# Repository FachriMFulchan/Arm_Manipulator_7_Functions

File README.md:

# Arm_Manipulator_7_Functions
Ini merupakan data dokumentasi dari Proyek Akhir kami yang berjudul "Rancang Bangun Arm Manipulator 7 Functions dan Master Controller" di Politeknik Manufaktur Negeri Bandung

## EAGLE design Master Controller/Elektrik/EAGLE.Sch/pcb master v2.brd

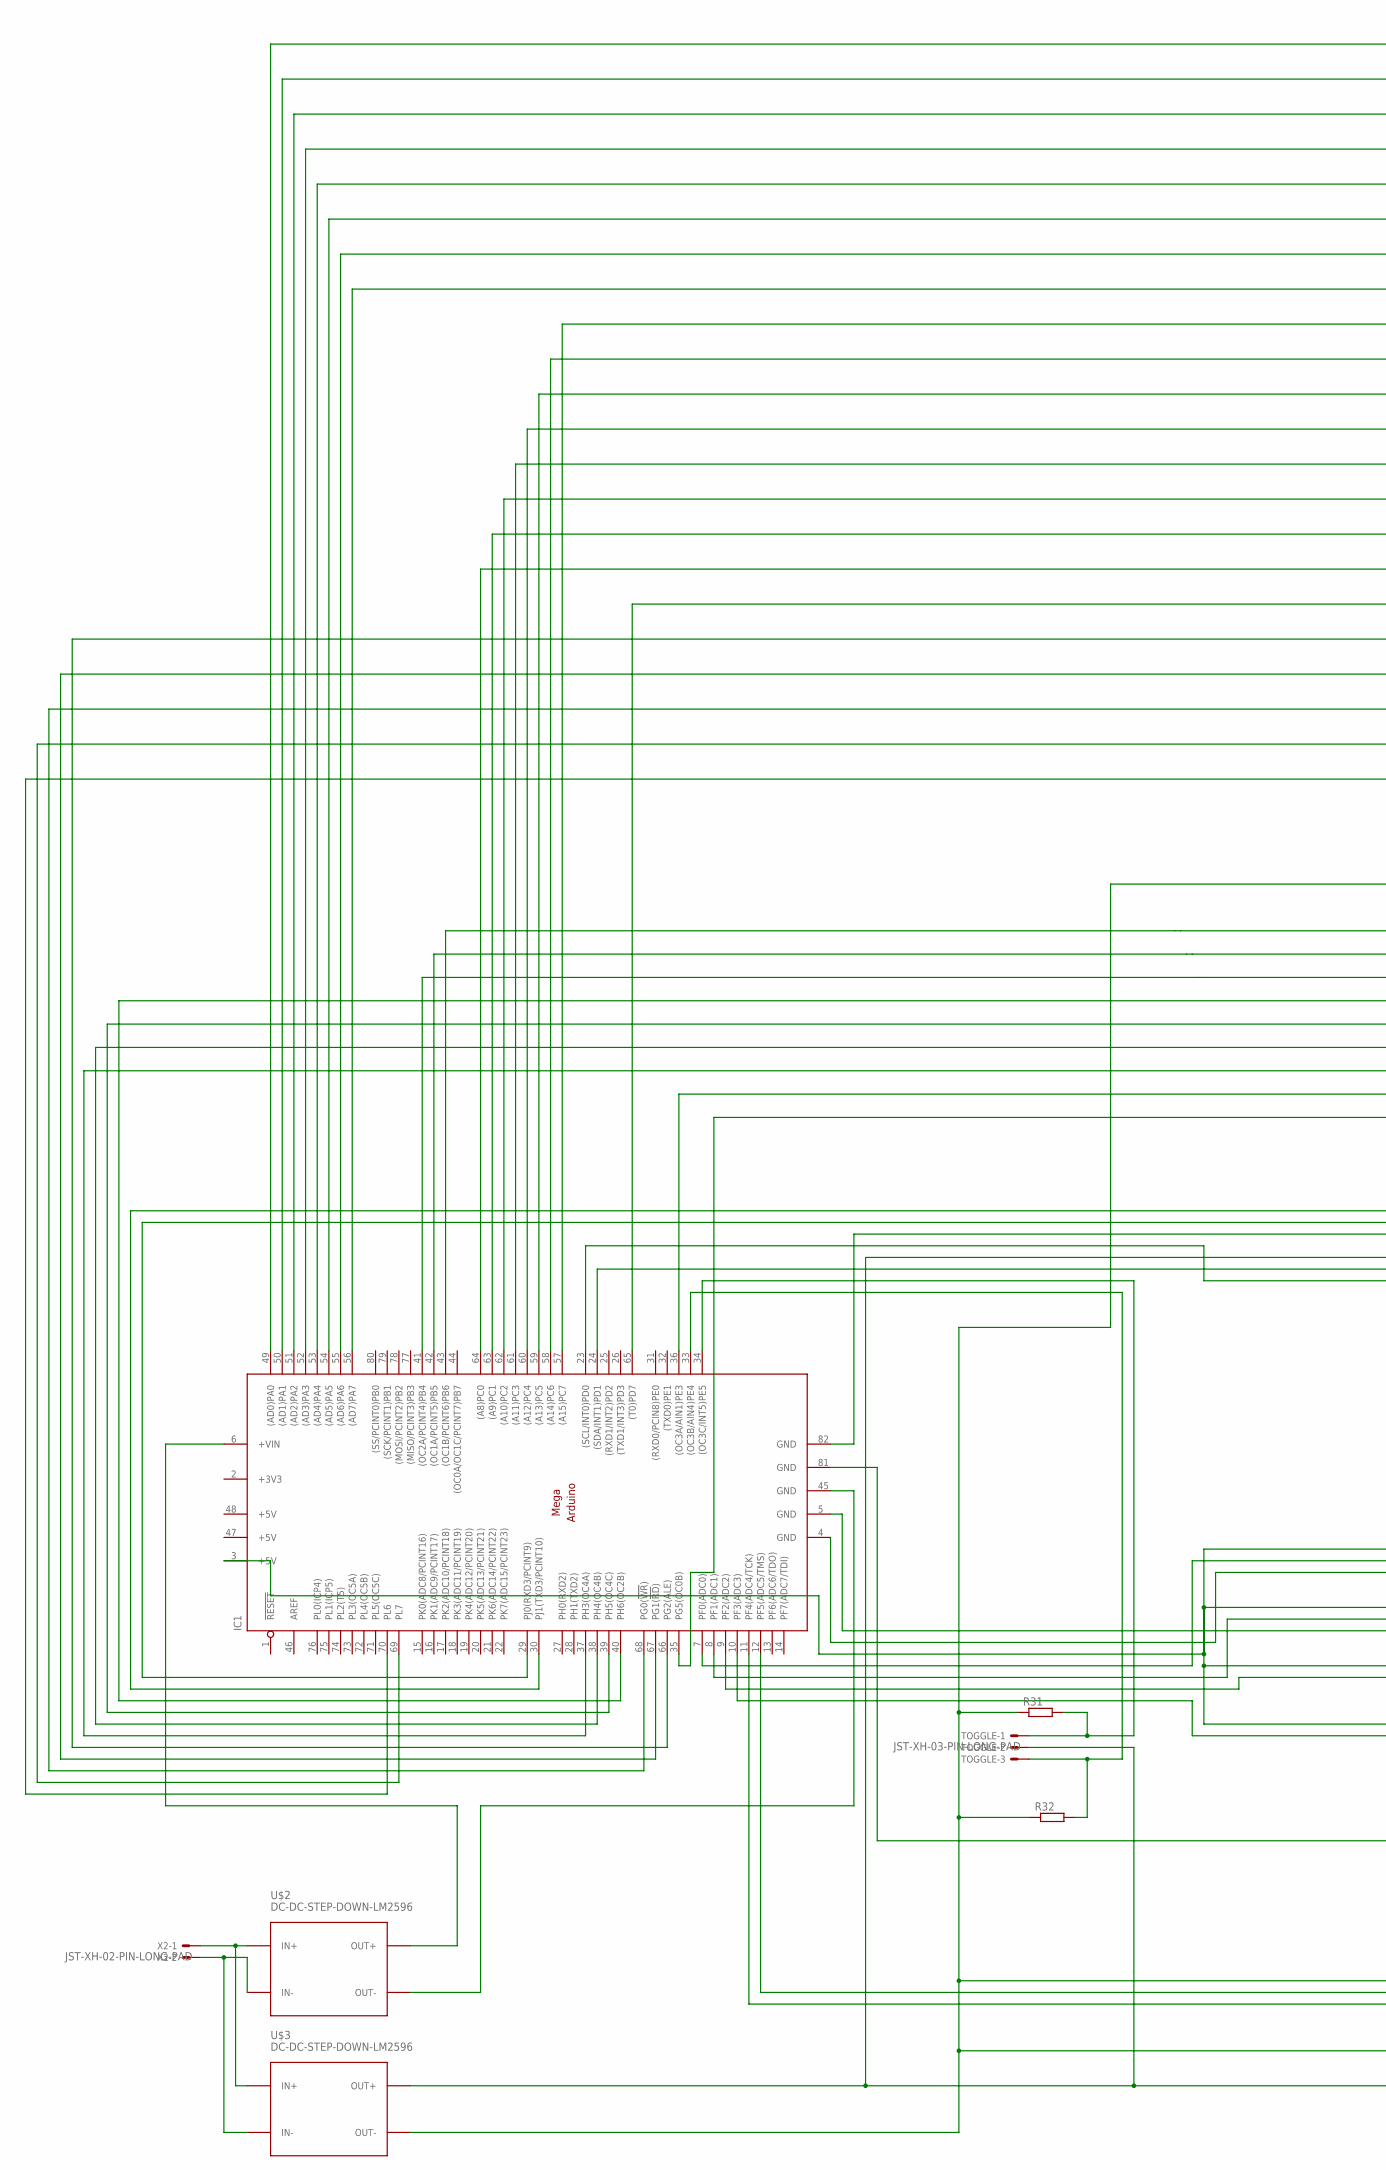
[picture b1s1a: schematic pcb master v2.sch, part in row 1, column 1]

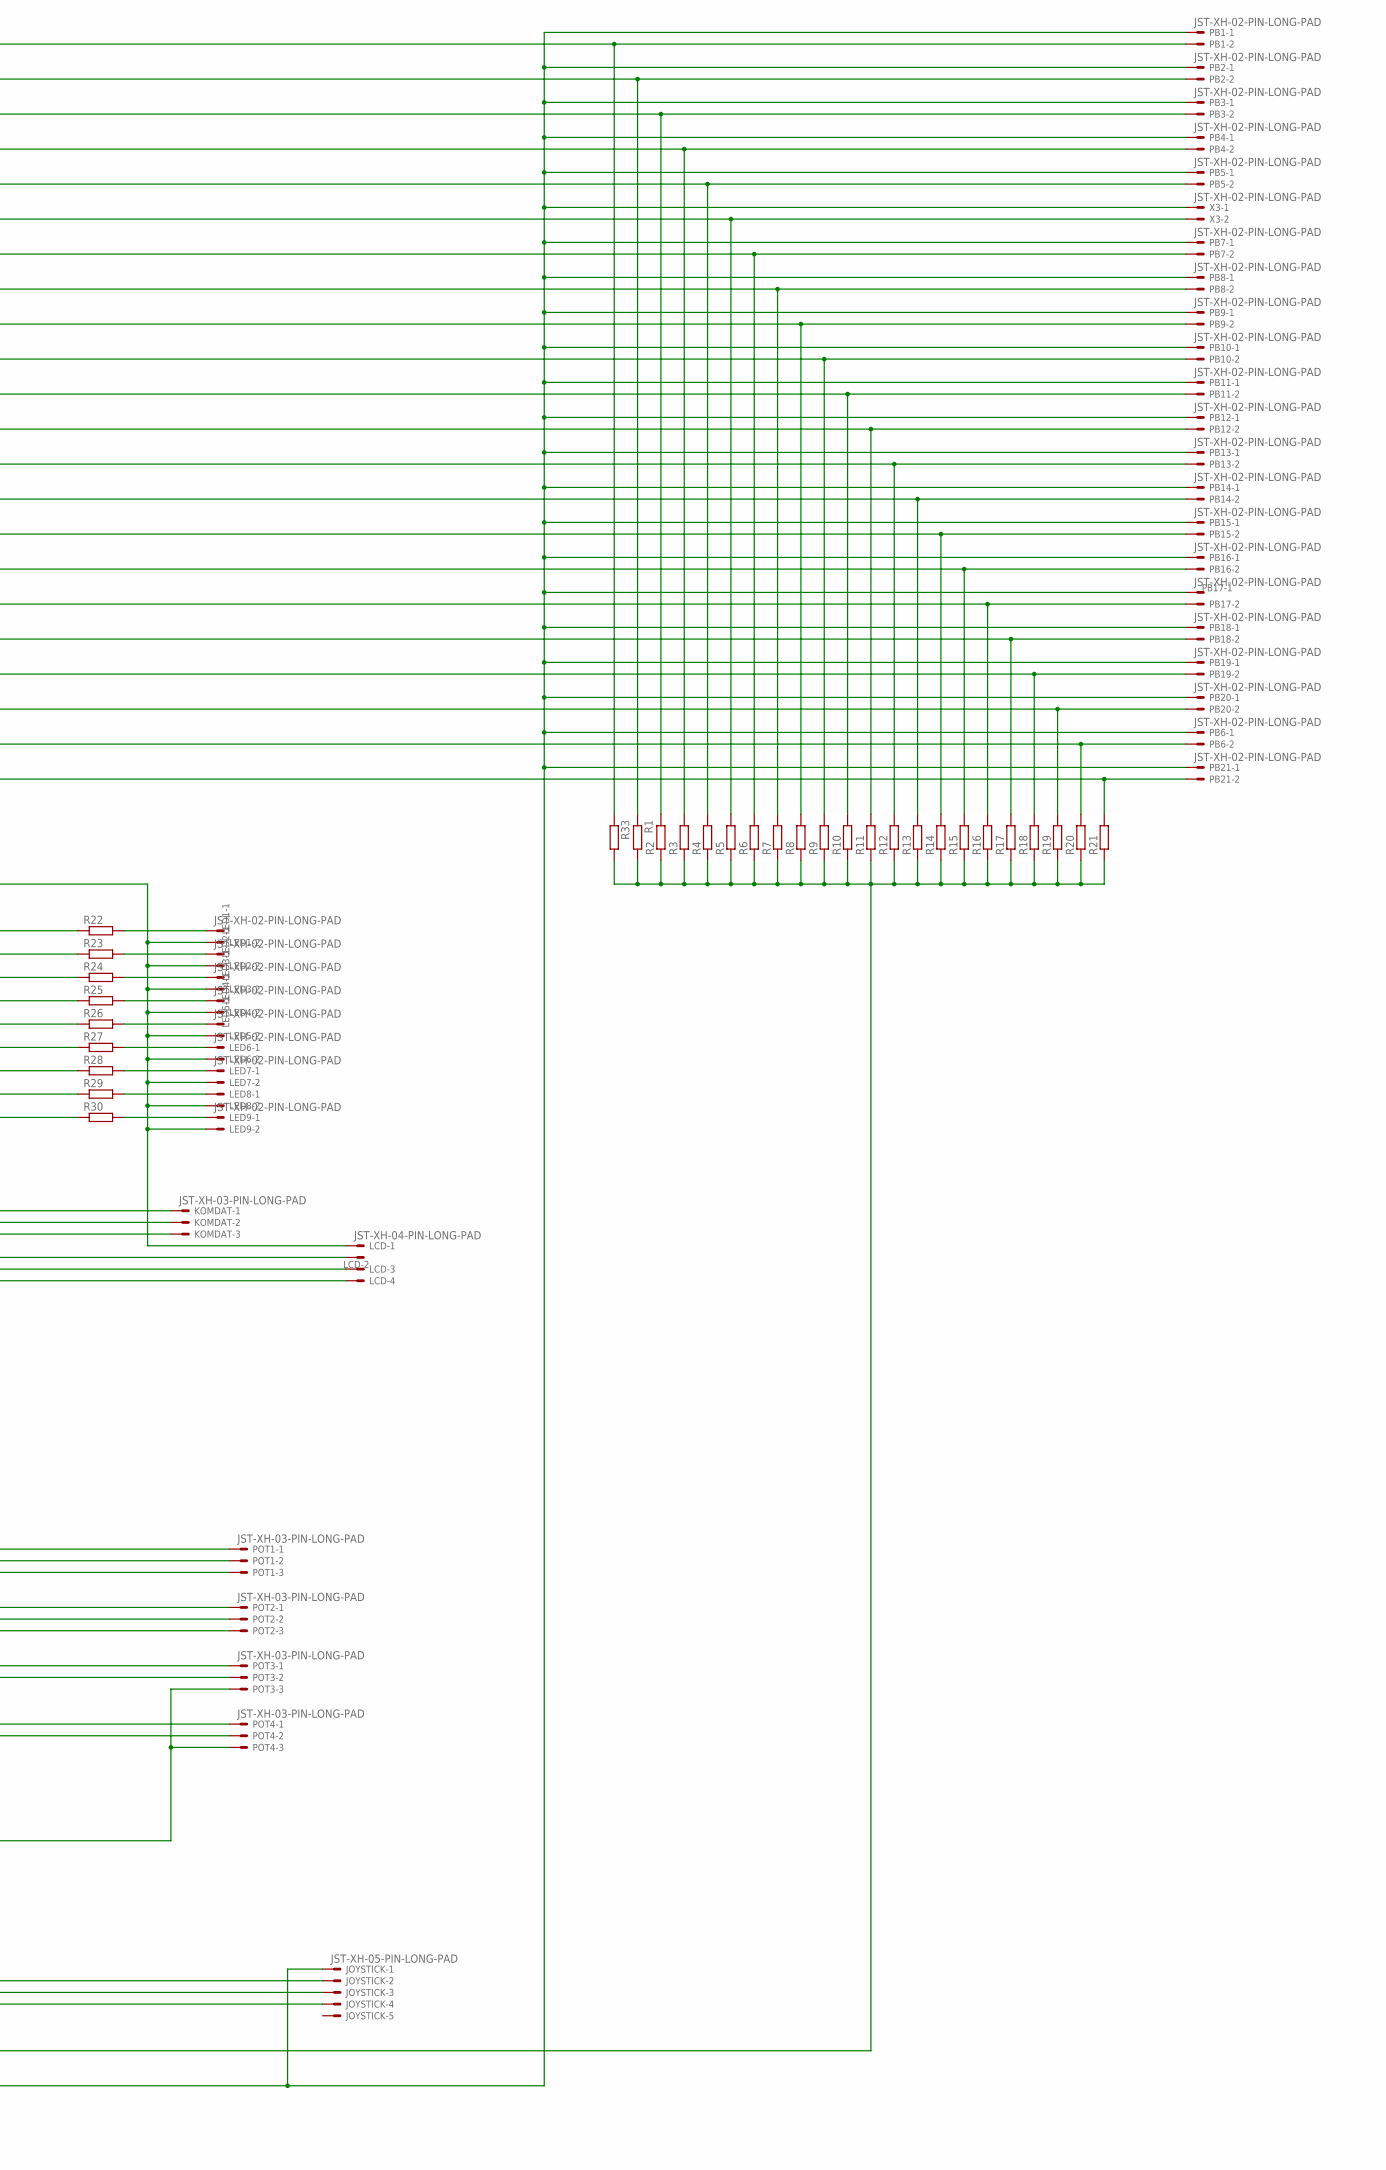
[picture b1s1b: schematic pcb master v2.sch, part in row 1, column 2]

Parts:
IC1: MEGAARDUINO_1; MEGA_ARDUINO
JOYSTICK: JST-XH-05-PIN-LONG-PAD; JST-XH-05-PACKAGE-LONG-PAD
KOMDAT: JST-XH-03-PIN-LONG-PAD; JST-XH-03-PACKAGE-LONG-PAD
LCD: JST-XH-04-PIN-LONG-PAD; JST-XH-04-PACKAGE-LONG-PAD
LED1, LED2, LED3, LED4, LED5, LED6, LED7, LED8, LED9: JST-XH-02-PIN-LONG-PAD; JST-XH-02-PACKAGE-LONG-PAD
PB1, PB2, PB3, PB4, PB5, PB6, PB7, PB8, PB9, PB10, PB11, PB12, PB13, PB14, PB15, PB16, PB17, PB18, PB19, PB20, PB21: JST-XH-02-PIN-LONG-PAD; JST-XH-02-PACKAGE-LONG-PAD
POT1, POT2, POT3, POT4: JST-XH-03-PIN-LONG-PAD; JST-XH-03-PACKAGE-LONG-PAD
R1, R2, R3, R4, R5, R6, R7, R8, R9, R10, R11, R12, R13, R14, R15, R16, R17, R18, R19, R20, R21, R22, R23, R24, R25, R26, R27, R28, R29, R30, R31, R32, R33: R-EU_0207/12; 0207/12
TOGGLE: JST-XH-03-PIN-LONG-PAD; JST-XH-03-PACKAGE-LONG-PAD
U$2, U$3: DC-DC-STEP-DOWN-LM2596
X2, X3: JST-XH-02-PIN-LONG-PAD; JST-XH-02-PACKAGE-LONG-PAD

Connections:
+3V3: IC1.2 (+3V3)
+5V: IC1.47 (+5V), IC1.48 (+5V)
unnamed: IC1.33 ((OC3B/AIN4)PE4), R32.2, TOGGLE.3
unnamed: U$2.IN+, U$3.IN+, X2.1
unnamed: U$2.IN-, U$3.IN-, X2.2
unnamed: IC1.60 ((A12)PC4), PB12.2, R11.2
unnamed: IC1.7 (PF0(ADC0)), POT1.2
unnamed: LED1.1, R22.2
unnamed: LED2.1, R23.2
unnamed: IC1.10 (PF3(ADC3)), POT4.2
unnamed: IC1.34 ((OC3C/INT5)PE5), R31.2, TOGGLE.1
unnamed: LED3.1, R24.2
unnamed: IC1.57 ((A15)PC7), PB9.2, R8.2
unnamed: IC1.8 (PF1(ADC1)), POT2.2
unnamed: IC1.9 (PF2(ADC2)), POT3.2
unnamed: IC1.82 (GND), KOMDAT.3
unnamed: IC1.11 (PF4(ADC4/TCK)), JOYSTICK.4
unnamed: IC1.81 (GND), POT3.3, POT4.3
unnamed: LED4.1, R25.2
unnamed: IC1.24 ((SDA/INT1)PD1), LCD.3
unnamed: IC1.23 ((SCL/INT0)PD0), LCD.4
unnamed: IC1.29 (PJ0(RXD3/PCINT9)), KOMDAT.2
unnamed: IC1.70 (PL6), PB21.2, R21.2
unnamed: IC1.59 ((A13)PC5), PB11.2, R10.2
unnamed: IC1.69 (PL7), PB6.2, R20.2
unnamed: IC1.45 (GND), U$2.OUT-
unnamed: JOYSTICK.2, LCD.1, LED1.2, LED2.2, LED3.2, LED4.2, LED5.2, LED6.2, LED7.2, LED8.2, LED9.2, R1.2, R2.1, R3.1, R4.1, R5.1, R6.1, R7.1, R8.1, R9.1, R10.1, R11.1, R12.1, R13.1, R14.1, R15.1, R16.1, R17.1, R18.1, R19.1, R20.1, R21.1, R31.1, R32.1, R33.2, U$3.OUT-
unnamed: LED7.1, R28.2
unnamed: IC1.6 (+VIN), U$2.OUT+
unnamed: IC1.65 ((T0)PD7), PB17.2, R16.2
unnamed: IC1.3 (+5V), POT1.1, POT2.1, POT3.1, POT4.1
unnamed: IC1.64 ((A8)PC0), PB16.2, R15.2
unnamed: IC1.30 (PJ1(TXD3/PCINT10)), KOMDAT.1
unnamed: IC1.66 (PG2(ALE)), PB18.2, R17.2
unnamed: IC1.12 (PF5(ADC5/TMS)), JOYSTICK.3
unnamed: IC1.54 ((AD5)PA5), R5.2, X3.2
unnamed: IC1.58 ((A14)PC6), PB10.2, R9.2
unnamed: IC1.49 ((AD0)PA0), PB1.2, R33.1
unnamed: IC1.68 (PG0(!WR!)), PB20.2, R19.2
unnamed: IC1.50 ((AD1)PA1), PB2.2, R1.1
unnamed: IC1.52 ((AD3)PA3), PB4.2, R3.2
unnamed: LED5.1, R26.2
unnamed: LED6.1, R27.2
unnamed: LED8.1, R29.2
unnamed: LED9.1, R30.2
unnamed: IC1.35 (PG5(OC0B)), R30.1
unnamed: IC1.36 ((OC3A/AIN1)PE3), R29.1
unnamed: IC1.37 (PH3(OC4A)), R28.1
unnamed: IC1.38 (PH4(OC4B)), R27.1
unnamed: IC1.39 (PH5(OC4C)), R26.1
unnamed: IC1.40 (PH6(OC2B)), R25.1
unnamed: IC1.41 ((OC2A/PCINT4)PB4), R24.1
unnamed: IC1.42 ((OC1A/PCINT5)PB5), R23.1
unnamed: IC1.43 ((OC1B/PCINT6)PB6), R22.1
unnamed: IC1.62 ((A10)PC2), PB14.2, R13.2
unnamed: IC1.56 ((AD7)PA7), PB8.2, R7.2
unnamed: IC1.4 (GND), POT1.3
unnamed: IC1.5 (GND), POT2.3
unnamed: IC1.61 ((A11)PC3), PB13.2, R12.2
unnamed: IC1.63 ((A9)PC1), PB15.2, R14.2
unnamed: IC1.67 (PG1(!RD!)), PB19.2, R18.2
unnamed: JOYSTICK.1, LCD.2, PB1.1, PB2.1, PB3.1, PB4.1, PB5.1, PB6.1, PB7.1, PB8.1, PB9.1, PB10.1, PB11.1, PB12.1, PB13.1, PB14.1, PB15.1, PB16.1, PB17.1, PB18.1, PB19.1, PB20.1, PB21.1, TOGGLE.2, U$3.OUT+, X3.1
unnamed: IC1.51 ((AD2)PA2), PB3.2, R2.2
unnamed: IC1.53 ((AD4)PA4), PB5.2, R4.2
unnamed: IC1.55 ((AD6)PA6), PB7.2, R6.2

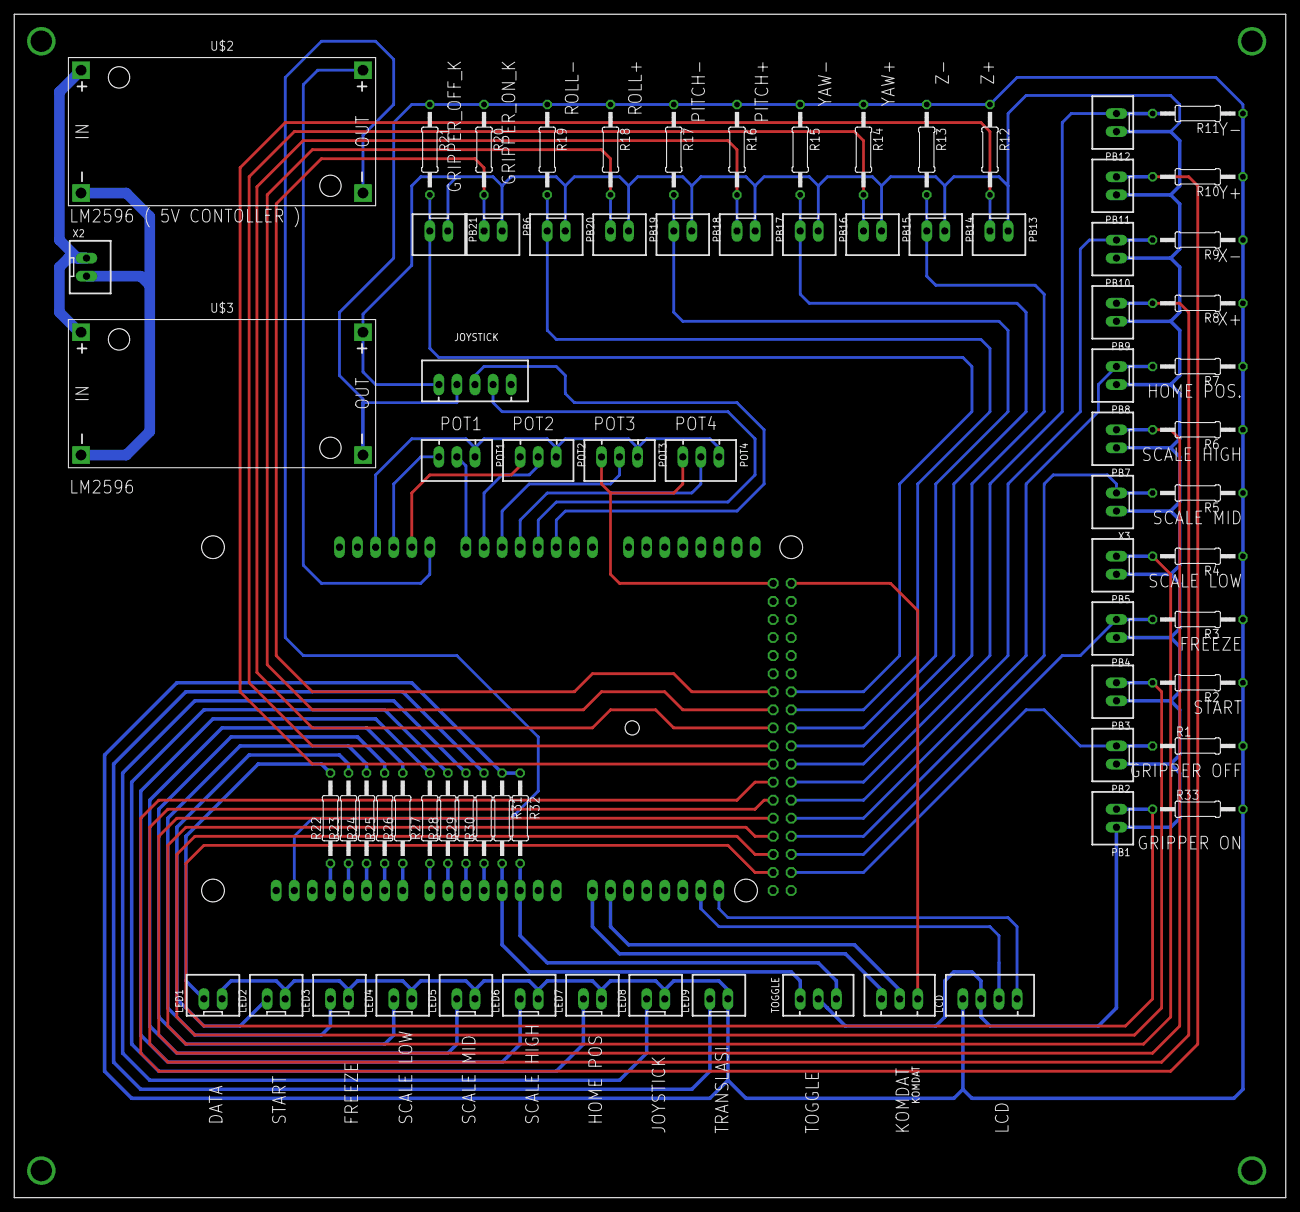
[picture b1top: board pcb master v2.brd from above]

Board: 2 copper layers, 178.7 x 166.4 mm, 76 parts (1 on the bottom side), 64 nets.

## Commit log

2022-08-19 Create KTI_&_Jurnal

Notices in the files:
parts and their libraries:
diy-modules: Released under the Creative Commons Attribution 4.0 International License: http://creativecommons.org/licenses/by/4.0
